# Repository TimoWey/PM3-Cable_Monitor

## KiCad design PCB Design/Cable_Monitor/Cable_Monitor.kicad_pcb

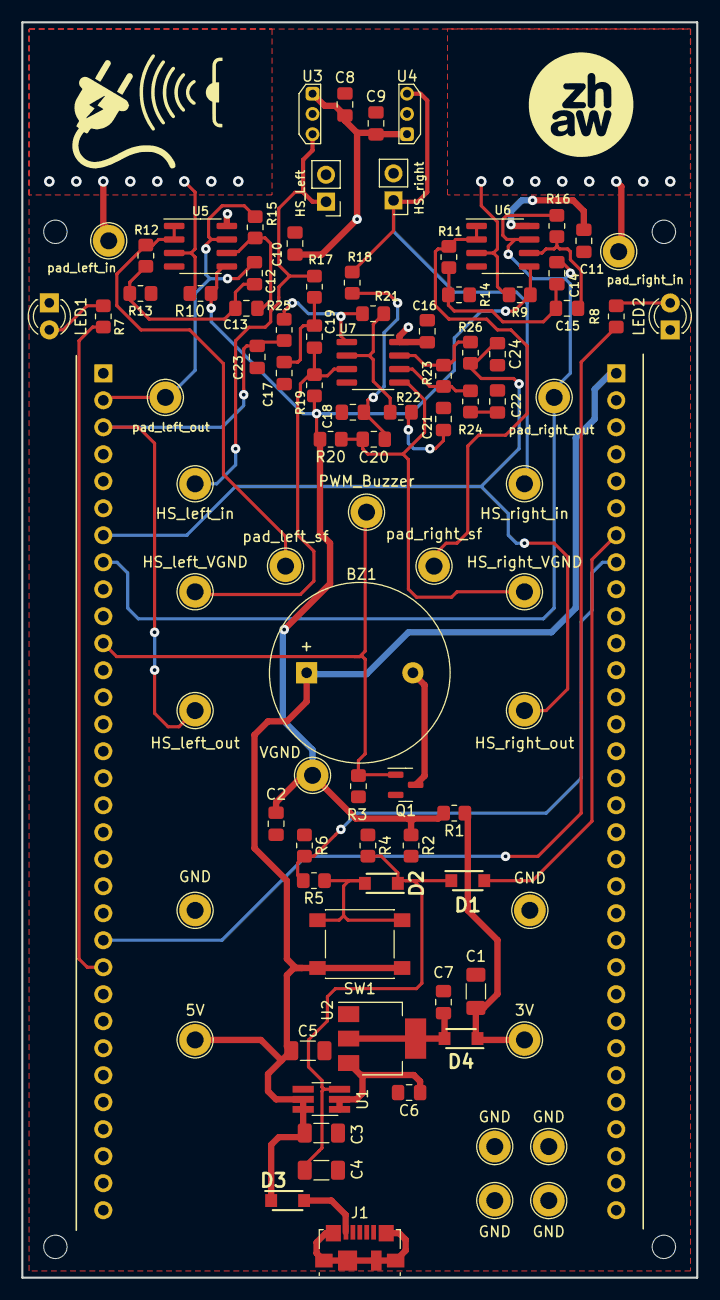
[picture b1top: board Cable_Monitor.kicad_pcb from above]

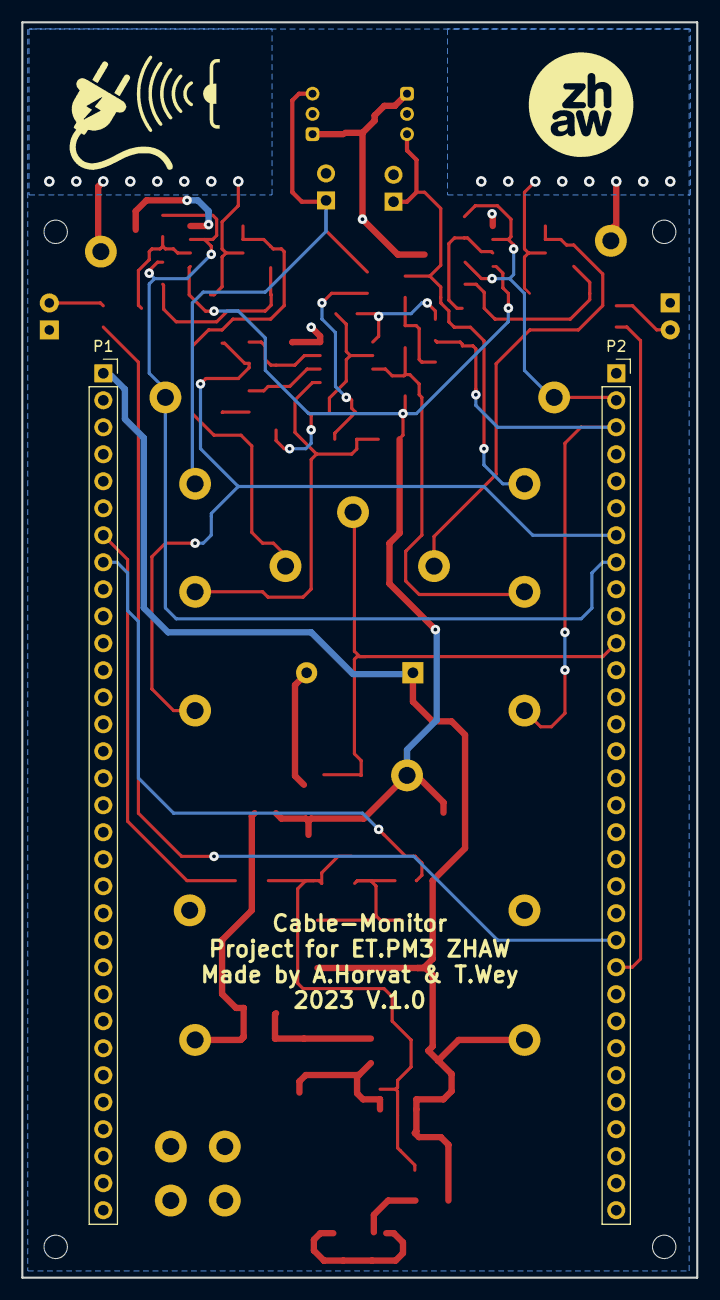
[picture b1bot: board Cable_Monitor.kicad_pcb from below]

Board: 2 copper layers, 63.5 x 118.1 mm, 97 parts (2 on the bottom side), 41 nets.

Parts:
BZ1: Buzzer; Buzzer_D14mm_H7mm_P10mm
C1, C4, C5: 100uF; C_1206_3216Metric_Pad1.33x1.80mm_HandSolder
C2: 220nF; C_0805_2012Metric_Pad1.18x1.45mm_HandSolder
C3: 4.7uF; C_1206_3216Metric_Pad1.33x1.80mm_HandSolder
C6, C8, C9, C17, C18, C23, C24: 100nF; C_0805_2012Metric_Pad1.18x1.45mm_HandSolder
C7, C19, C20, C21, C22: 10uF; C_0805_2012Metric_Pad1.18x1.45mm_HandSolder
C10, C11, C16: 100n; C_0805_2012Metric_Pad1.18x1.45mm_HandSolder
C12, C14: 18nF; C_0805_2012Metric_Pad1.18x1.45mm_HandSolder
C13, C15: 330nF; C_0805_2012Metric_Pad1.18x1.45mm_HandSolder
D1, D2, D3, D4: SS13L_R3G; SODFL3618X143N
H1, H2, H3, H4: MountingHole; MountingHole_2.2mm_M2
HS_Left: Conn_01x02_Male; PinHeader_1x02_P2.54mm_Vertical
HS_right: Conn_01x02_Male; PinHeader_1x02_P2.54mm_Vertical
J1: USB_B_Micro; USB_Micro-B_Molex_47346-0001
LED1, LED2: LEDred_3mm; LED_D3.0mm
P1, P2: type="R" model="Conn_01x32_Female" lib=""; PinSocket_1x32_P2.54mm_Vertical
Q1: BSS316N; SOT-23
R1, R2, R4: 10k; R_0805_2012Metric_Pad1.20x1.40mm_HandSolder
R3, R19, R20: 100k; R_0805_2012Metric_Pad1.20x1.40mm_HandSolder
R5: 30k; R_0805_2012Metric_Pad1.20x1.40mm_HandSolder
R6: 43k; R_0805_2012Metric_Pad1.20x1.40mm_HandSolder
R7, R8: 62; R_0805_2012Metric_Pad1.20x1.40mm_HandSolder
R9, R10, R21, R23: 1M; R_0805_2012Metric_Pad1.20x1.40mm_HandSolder
R11, R12: 5.1k; R_0805_2012Metric_Pad1.20x1.40mm_HandSolder
R13, R14: 7.5k; R_0805_2012Metric_Pad1.20x1.40mm_HandSolder
R15, R16: 560k; R_0805_2012Metric_Pad1.20x1.40mm_HandSolder
R17, R18, R25, R26: 18k; R_0805_2012Metric_Pad1.20x1.40mm_HandSolder
R22, R24: 1k; R_0805_2012Metric_Pad1.20x1.40mm_HandSolder
SW1: On / Off Button; SW_SPST_PTS645
TP1, TP2, TP3, TP4, TP5, TP6: GND; TestPoint_Loop_D2.60mm_Drill1.6mm_Beaded
TP7: PWM_Buzzer; TestPoint_Loop_D2.60mm_Drill1.6mm_Beaded
TP8: VGND; TestPoint_Loop_D2.60mm_Drill1.6mm_Beaded
TP9: pad_left_in; TestPoint_Loop_D2.60mm_Drill1.6mm_Beaded
TP10: pad_right_in; TestPoint_Loop_D2.60mm_Drill1.6mm_Beaded
TP11: 5V; TestPoint_Loop_D2.60mm_Drill1.6mm_Beaded
TP12: pad_left_out; TestPoint_Loop_D2.60mm_Drill1.6mm_Beaded
TP13: pad_right_out; TestPoint_Loop_D2.60mm_Drill1.6mm_Beaded
TP14: 3V; TestPoint_Loop_D2.60mm_Drill1.6mm_Beaded
TP15: HS_left_in; TestPoint_Loop_D2.60mm_Drill1.6mm_Beaded
TP16: HS_right_in; TestPoint_Loop_D2.60mm_Drill1.6mm_Beaded
TP17: HS_left_out; TestPoint_Loop_D2.60mm_Drill1.6mm_Beaded
TP18: HS_right_out; TestPoint_Loop_D2.60mm_Drill1.6mm_Beaded
TP19: pad_left_sf; TestPoint_Loop_D2.60mm_Drill1.6mm_Beaded
TP20: pad_right_sf; TestPoint_Loop_D2.60mm_Drill1.6mm_Beaded
TP21: HS_left_VGND; TestPoint_Loop_D2.60mm_Drill1.6mm_Beaded
TP22: HS_right_VGND; TestPoint_Loop_D2.60mm_Drill1.6mm_Beaded
U1: SiP32508; TSOT-23-6_HandSoldering
U2: LD1117S33TR; SOT-223-3_TabPin2
U3, U4: DRV5053_THT; TO-92Flat_wide
U5, U6, U7: MCP6002-xSN; SOIC-8_3.9x4.9mm_P1.27mm

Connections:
+3V0: C1.1, C8.2, C9.2, C10.1, C11.1, C16.1, D4.1 (K), P2.1, R1.1, TP14.1, U3.1 (VCC), U4.1 (VCC), U5.8 (V+), U6.8 (V+), U7.8 (V+)
+5V: BZ1.1 (-), C3.1, C5.1, D3.1 (K), P1.1, SW1.2, TP11.1, U1.5 (IN), U1.6 (IN)
/hall-sensor_left_right/in_left: HS_Left.1, R17.1, TP15.1, U3.3 (OUT)
/hall-sensor_left_right/in_right: HS_right.1, R18.1, TP16.1, U4.3 (OUT)
Enable: C4.1, D1.1 (K), D2.1 (K), R4.2, U1.3 (EN)
GND: C1.2, C2.2, C3.2, C4.2, C5.2, C6.2, C7.2, C8.1, C9.1, C10.2, C11.2, C16.2, C17.1, C18.1, C21.2, C22.2, C23.2, C24.2, HS_Left.2, HS_right.2, J1.5 (GND), LED1.1 (K), LED2.1 (K), P1.32, P2.6, P2.15, P2.32, Q1.2 (S), R2.2, R3.2, R4.1, R6.1, R13.2, R14.2, TP1.1, TP2.1, TP3.1, TP4.1, TP5.1, TP6.1, U1.4 (GND), U2.1 (GND), U3.2 (GND), U4.2 (GND), U5.4 (V-), U6.4 (V-), U7.4 (V-)
unnamed: BZ1.2 (+), Q1.3 (D)
unnamed: C12.1, C13.1, R12.2, R13.1
unnamed: C14.1, C15.1, R11.2, R14.1
unnamed: C17.2, C19.1, R17.2
unnamed: C18.2, C20.1, R18.2
unnamed: C21.1, R22.2
unnamed: C22.1, R24.2
unnamed: D2.2 (A), R5.1, SW1.1
unnamed: D3.2 (A), J1.1 (VBUS)
unnamed: C7.1, D4.2 (A), U2.2 (VO)
unnamed: LED1.2 (A), R7.2
unnamed: LED2.2 (A), R8.2
unnamed: R21.1, R25.1, U7.1
unnamed: R23.1, R26.1, U7.7
unnamed: C6.1, U1.1 (OUT), U1.2 (OUT), U2.3 (VI)
unnamed: R12.1, TP19.1, U5.1, U5.2 (-)
unnamed: C13.2, R15.2, U5.6 (-)
unnamed: R11.1, TP20.1, U6.1, U6.2 (-)
unnamed: C15.2, R16.2, U6.6 (-)
unnamed: C19.2, R19.1, TP21.1, U7.3 (+)
unnamed: R21.2, R22.1, U7.2 (-)
unnamed: C20.2, R20.1, TP22.1, U7.5 (+)
unnamed: R23.2, R24.1, U7.6 (-)
PA5: P2.11, Q1.1 (G), R3.1, TP7.1
PC1_: C24.1, P2.7, R26.2, TP18.1
PC3: C14.2, P2.8, R16.1, TP13.1, U6.7
PE3: P1.8, R5.2, R6.2
PE5: D1.2 (A), P1.7
PE13_: P2.22, R8.1
PE15_: P2.23, R7.1
PF6: C12.2, P2.2, R15.1, TP12.1, U5.7
PF8_: C23.1, P2.3, R25.2, TP17.1
VGND: C2.1, R1.2, R2.1, R9.2, R10.2, R19.2, R20.2, TP8.1, U5.5 (+), U6.5 (+)
pad_left: R10.1, TP9.1, U5.3 (+)
pad_right: R9.1, TP10.1, U6.3 (+)

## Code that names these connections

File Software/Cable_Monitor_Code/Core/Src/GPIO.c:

/** ***************************************************************************
 * @file
 * @brief USER pushbutton
 *
 * Initializes the GPIO for the pushbutton.
 * @n Enables the interrupt on the pushbutton.
 * @n Implements the interrupt handler for the pushbutton.
 *
 * @author  Hanspeter Hochreutener, hhrt@zhaw.ch
 * @date	16.04.2020
 *****************************************************************************/

/******************************************************************************
 * Includes
 *****************************************************************************/
#include "stm32f4xx.h"
#include "stm32f429i_discovery.h"

#include "GPIO.h"

/******************************************************************************
 * Defines
 *****************************************************************************/

/******************************************************************************
 * Variables
 *****************************************************************************/

/******************************************************************************
 * Functions
 *****************************************************************************/

/** ***************************************************************************
 * @brief Configure the GPIO for the USER pushbutton
 *
 * The USER pushbutton is connected to PA0.
 *****************************************************************************/
void GPIO_Init(void) {
	// Configure PE5 as Output
	/*__HAL_RCC_GPIOG_CLK_ENABLE();
	 GPIOE-> MODER |= 0x400;
	 GPIOE-> OSPEEDR |= 0x400;
	 HAL_GPIO_WritePin(GPIOE, GPIO_PIN_5, GPIO_PIN_SET);*/

	// Initialize the GPIO pins
	GPIO_InitTypeDef GPIO_InitStruct;
	__HAL_RCC_GPIOE_CLK_ENABLE(); // Enable the GPIO E clock

	// Configure PE3 in input mode
	GPIO_InitStruct.Pin = PIN_PE3;
	GPIO_InitStruct.Mode = GPIO_MODE_INPUT;
	GPIO_InitStruct.Pull = GPIO_PULLDOWN;
	HAL_GPIO_Init(GPIOE, &GPIO_InitStruct);

	// Configure PE5 in output push-pull mode -> Soft latching power Circuit drive (Keeps board On)
	GPIO_InitStruct.Pin = PIN_PE5;
	GPIO_InitStruct.Mode = GPIO_MODE_OUTPUT_PP;
	GPIO_InitStruct.Pull = GPIO_NOPULL;
	GPIO_InitStruct.Speed = GPIO_SPEED_FREQ_LOW;
	HAL_GPIO_Init(GPIOE, &GPIO_InitStruct);

	// Configure PE15 in output push-pull mode -> Used for LED_1 (Right LED)
	GPIO_InitStruct.Pin = LED_RIGHT;
	GPIO_InitStruct.Mode = GPIO_MODE_OUTPUT_PP;
	GPIO_InitStruct.Pull = GPIO_NOPULL;
	GPIO_InitStruct.Speed = GPIO_SPEED_FREQ_HIGH;
	HAL_GPIO_Init(GPIOE, &GPIO_InitStruct);

	// Configure PE13 in output push-pull mode -> Used for LED_2 (Left LED)
	GPIO_InitStruct.Pin = LED_LEFT;
	GPIO_InitStruct.Mode = GPIO_MODE_OUTPUT_PP;
	GPIO_InitStruct.Pull = GPIO_NOPULL;
	GPIO_InitStruct.Speed = GPIO_SPEED_FREQ_HIGH;
	HAL_GPIO_Init(GPIOE, &GPIO_InitStruct);

	// Automatically Keeps Board alive (Soft latching circuit) by setting PIN5->High
	HAL_GPIO_WritePin(GPIOE, GPIO_PIN_5, GPIO_PIN_SET);
	while (HAL_GPIO_ReadPin(GPIOE, PIN_PE3) == GPIO_PIN_SET) {
		HAL_Delay(100);
	}
	HAL_Delay(3000);
}

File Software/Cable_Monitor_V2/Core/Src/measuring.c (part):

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 * @n At each trigger all inputs are converted sequentially
 * and transfered to memory by the DMA.
 * @n The DMA triggers the transfer complete interrupt when all data is ready.
 * @n The inputs used are ADC123_IN13 = GPIO PC3, ADC3_IN4 = GPIO PF6,
 * ADC123_IN11 = GPIO PC1 and ADC3_IN6 = GPIO PF8.
 *****************************************************************************/
static void MEAS_ADC3_IN13_IN4_IN11_IN6_scan_init(void)
{
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 * @brief Configure GPIOs in analog mode.
 *
 * @note The input number for the ADCs is not equal to the GPIO pin number!
 * - ADC3_IN4 = GPIO PF6
 * - ADC123_IN13 = GPIO PC3
 *****************************************************************************/
void MEAS_GPIO_analog_init(void)
{
	__HAL_RCC_GPIOF_CLK_ENABLE();		// Enable Clock for GPIO port F
	GPIOF->MODER |= (GPIO_MODER_MODER6_Msk);// Analog mode for PF6 = ADC3_IN4
	__HAL_RCC_GPIOC_CLK_ENABLE();		// Enable Clock for GPIO port C
	GPIOC->MODER |= (GPIO_MODER_MODER3_Msk);// Analog mode for PC3 = ADC123_IN13
}


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
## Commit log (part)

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2023-10-13 software gugus
2023-10-13 Final Design Done
2023-10-13 Done with PCB Design V1.0
2023-10-20 3d files
2023-10-20 report fertig
2023-10-20 Bom und Image
2023-10-20 BOM usw
2023-10-23 mööööh
2023-10-23 saftig
2023-10-23 abstract done and gitignore
2023-10-23 introduction finished
2023-10-23 introduction added and finished, specification added WIP
2023-10-23 crazy pics
2023-10-23 dupps duppa gantttttttttttttttt
2023-10-23 Push
2023-10-25 calculation
2023-10-25 pushi
2023-10-27 korrigierter text vom Mat TOP G
2023-10-27 LOLOLO
2023-10-28 pushi kurac
2023-11-02 Backup Schematics
2023-11-02 ladlosas
2023-11-02 Schema für Messung
2023-11-02 suppa code geshriben
2023-11-02 Unbennent
2023-11-03 Load Switch code fix
2023-11-03 Schematics Update and measurement Demo
2023-11-03 gitignore
2023-11-10 simulation matlab und spice
2023-11-11 messungen
2023-11-11 bilder gantt etc
2023-11-12 HW report done
2023-11-17 Amp Detection Script
2023-11-17 Set up project
2023-11-17 started implementing the menu switchcase
2023-11-24 Branchy
2023-11-24 gugus
2023-11-24 copypasta
2023-11-24 GPIO
2023-11-24 Revert "Branchy"
    This reverts commit 4ddf2e682ee2b218aa63f2b84ef7dd3e2dd7838d.
2023-11-24 Revert "Branchy"
    This reverts commit 77043ae8ee52b0a20f0d0a708fc1d9c6624f671d.
2023-11-24 Grundgerüst
2023-11-24 fortschritt switch case
2023-11-26 gitignore update
2023-11-26 somewhat working state machine(GUI)
2023-11-26 state maschine progress
2023-11-28 state machine basics done
2023-11-29 vscode debugging
2023-11-30 vs code annoying
2023-12-01 touchGFX project init
2023-12-01 first menu done
2023-12-01 basic menu done, code generated
2023-12-01 GUI progress
2023-12-02 Branchie
2023-12-02 Yolo
2023-12-02 on off button
2023-12-02 pins for on off defined in mx
2023-12-03 power led working, pe13 set high
    device can be powered on with the button on the extender board, in init function the PE5 is set to high. also PE13 is set to high indicating device ON
2023-12-03 device can be turned off via button
    implemented ISR for button on sub print... device wil turn off when pressed for atleast 200ms
2023-12-03 added shutdown screen and shutdown touch button is wokring
    added windows shutdown screen when shutoff button is pressed. also PE5 is pulled low when shutoff button is pressed on the screen
2023-12-04 played around with gauge layout and displaying current etc
2023-12-04 adjustments
2023-12-04 hearthbeat and timeout
    1 second heartbeat implemented on userled and screentimout to 60 seconds. touch reset must be implemented
2023-12-04 sleep timout progress
    almost done with displaying the value on the gui
2023-12-04 presenter progress
2023-12-04 Measurement Setup for Presentation
    Outputs Raw Value of peaks, frequency and plots all ADC Channels
2023-12-04 Done visualitation
2023-12-05 gauge display value workd
    i was able to display the timeout value on the temporary gauge in main view
2023-12-05 displaying timout on GUI works
    displaying the timout value on the GUI works, included hearthbeat in FREERTOS task -> removed TIM7 since its useless now
2023-12-05 timeout reset when touched + transition added
    finally the timeout is being reset to 60 when the display is touched, also a shutdown transition was added when the timeout runs out
2023-12-05 fixed all nasty code -> simulation is again possible in parallel
    used #ifndef SIMULATION so differentiate between IDE and sumulation
2023-12-05 gui progress
    implemented both single and accurate menus completely
2023-12-05 small fixed, second screen with timeout implement
    added the sleep timeout to the second sreen as test, some small fixed
2023-12-06 timeout function now displayed in info menu aswell
2023-12-06 timeout added to menus
    now all relevant menus show the timeout
2023-12-06 added calibration_pad menu
    added another calibration pad menu and fixed some text issues
2023-12-06 hall menu added
    added last menu for hall sensor calibration
2023-12-07 Testing
2023-12-08 PUSH CAP
2023-12-08 include verhengt huso
2023-12-08 Buggy Woogie Demo Ready
2023-12-08 Presentation Ready
2023-12-08 displaying values through callback
    trying to display a placeholder value through callback method
2023-12-08 displaying values works
    now voltage, current frequency and the angle on the gauge can be displayed with a callback
2023-12-08 working, pro .c import
2023-12-08 Signal Strength and Main Frequency Function added
    Edited the main_frequency function to allow us to calculate the signal strenght.
    Added Struct to call and get the necessary values easily -> Code more readable
    @todo
    Find out how calibration is done -> enable to calculate distance and angle
2023-12-08 lib fix
2023-12-08 measureing and claculation inclusion works
2023-12-08 some progress
2023-12-11 some debugging
2023-12-11 bwoken
2023-12-11 debugging
2023-12-11 dma adc debugging
2023-12-12 debugging again
2023-12-12 dubugging disabled tim1-3 and dma2 mx
2023-12-12 super duper code
2023-12-12 typo corrected
2023-12-12 code cleanup
2023-12-12 increased touchgfx tick calling
2023-12-16 gui progress, but display buggy
2023-12-17 added scrolling menu in calubvration pad
2023-12-17 removed unnecessary resources
2023-12-17 flash storing works in last sector
2023-12-18 write values from flash to swipecontainer successful
2023-12-18 deleted unnecessary calibration screens
2023-12-18 deleted hall calibration screen
2023-12-18 overwrite flash values from gui works
2023-12-18 left pad code advanced
2023-12-18 added hall calibartion menus
2023-12-18 Distance Calculation
2023-12-18 pads flash value works
2023-12-18 all calibration settings work
2023-12-18 TIM14 PWM for Buzzer on PA7
2023-12-18 pwm progress and button image
2023-12-19 Coefficients adapted
2023-12-19 pwm 4khz
2023-12-20 pwm for led setup
2023-12-20 included ale's calculations
2023-12-20 GUI update
2023-12-20 Reworked whole Calculation file
2023-12-20 GUI DONE & PROJECT CLEANUP
2023-12-20 Added whole lotta stuff
2023-12-20 Added Accurate FFT reading -> for Calibration
2023-12-20 updated calibration
2023-12-20 worked on callback for coefficients - WIP
2023-12-21 Added Accurate FFT calculation (used for Calibration)
2023-12-21 callback to coefficient function works
2023-12-21 calc coeff from ale
2023-12-21 distance value cap
2023-12-21 small fixed (timeout) and code cleanup
2023-12-22 typos
2023-12-22 bug fixing
2023-12-22 UPDATO
2023-12-22 Leck mio am arscho
2023-12-22 coeff added
2023-12-23 Current Aprox, needs to be tested
2023-12-23 Filled 3Phase menus and added measurement parameter for single and 3 phase
    Needs to be tested
2023-12-23 Work in Progress
2023-12-23 Push, tests was good habibi
2023-12-23 TouchGFX Updated
2023-12-23 flash erweitert
2023-12-23 load transition fixed
2023-12-23 POSH
2023-12-23 gui toggle added
2023-12-23 settings icon
2023-12-23 settings icon changed
2023-12-23 white settings icon
2023-12-23 new settings icon added
2023-12-25 PWM implemented with toggle button menu
2023-12-25 Current Calculation optimized
2023-12-25 Added Error Testing and Outputting to calculation.c
2023-12-25 Added Error Detection and Implemented the output of the error on the respective View.cpp file
2023-12-25 Added Error Detection and Outputting of errors
    Changed wildcard so that Einheit isn't being printed from wildcard, sondern from View.cpp float print instead
2023-12-25 pwm for LED works
2023-12-25 Updated Docs headers and added calibration measurement loops
2023-12-25 MASHALLAH
2023-12-25 doxymoxy
2023-12-25 touchgfx included suppa sache
2023-12-25 copilot goes brrrrrrrrrrrrrrrrt
2023-12-26 logo added
2023-12-26 Image ordner
2023-12-26 supi dupi yippue ayeeey
2023-12-26 mainpage imporovementsssssssssss
2023-12-26 Grafike
2023-12-26 testing edited
2023-12-26 testing witer
2023-12-26 GRAPH VIZ
2023-12-26 PUSHI KURAC
    Done mit Calculation und Measuring c dokumentierung
2023-12-27 fixed flash issue
2023-12-27 pushii
2023-12-27 testing continued, bug in accurate meas
2023-12-27 testing and main.c comments
2023-12-27 almost done
2023-12-27 I guess its kinda done
2023-12-27 Push Main screen plus GUI Funktione Doku
2023-12-27 logo2
2023-12-27 Last Push (hopefully)
2023-12-27 Sorry last push
